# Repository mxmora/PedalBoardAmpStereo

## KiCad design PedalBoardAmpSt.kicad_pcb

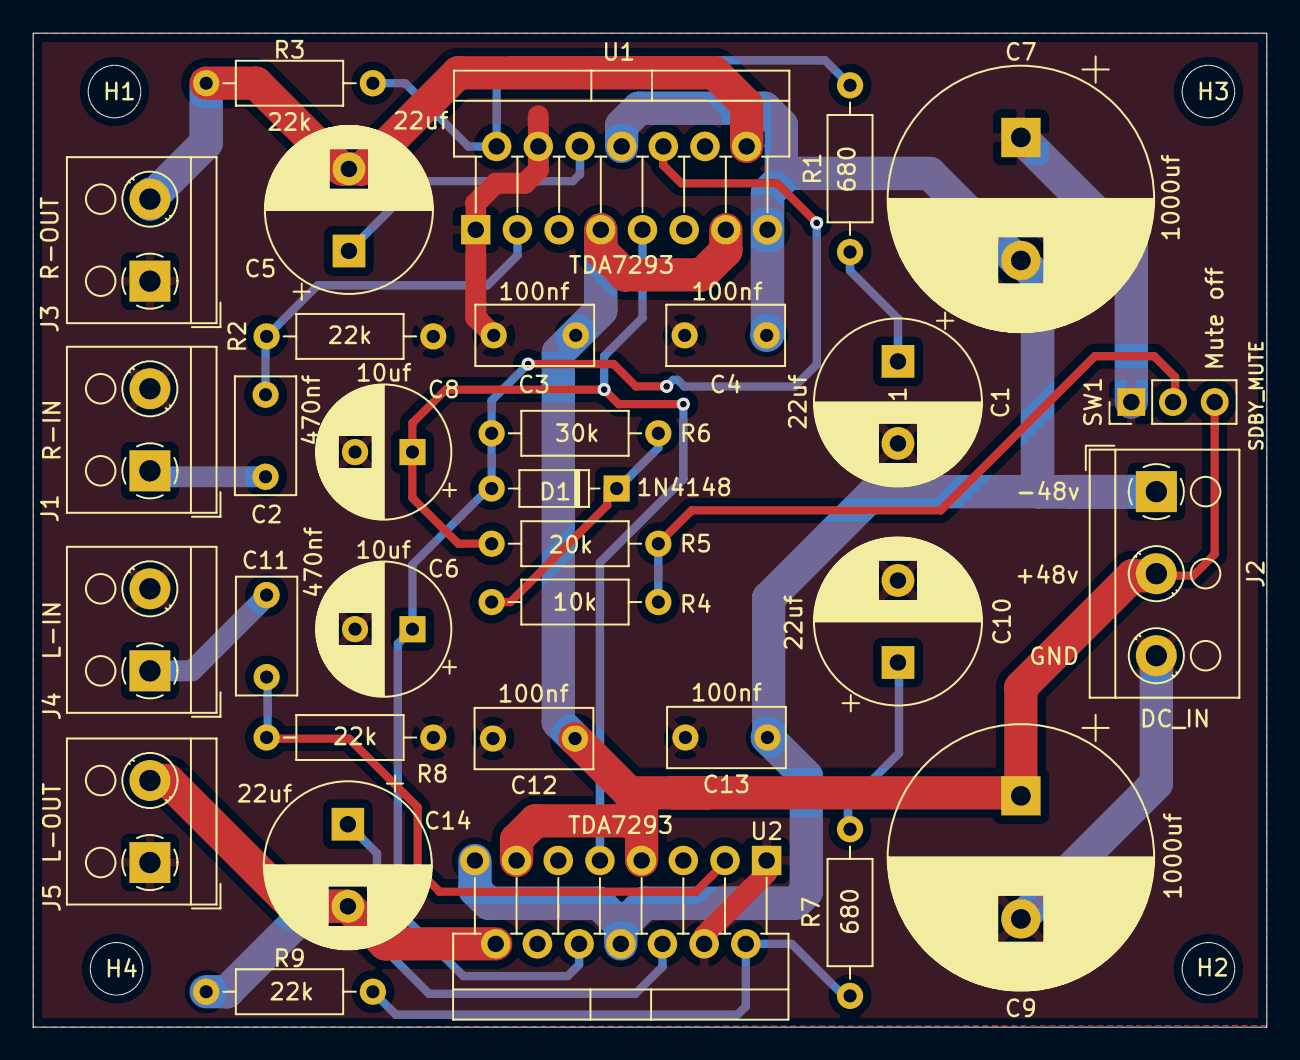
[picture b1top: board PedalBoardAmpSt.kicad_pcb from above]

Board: 2 copper layers, 75.2 x 60.6 mm, 36 parts (0 on the bottom side), 19 nets.

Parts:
C1, C5, C10, C14: 22uf; CP_Radial_D10.0mm_P5.00mm
C2, C11: 470nf; C_Rect_L7.0mm_W3.5mm_P5.00mm
C3, C4, C12, C13: 100nf; C_Rect_L7.0mm_W3.5mm_P5.00mm
C6, C8: 10uf; CP_Radial_D8.0mm_P3.50mm
C7, C9: 1000uf; CP_Radial_D16.0mm_P7.50mm
D1: 1N4148; D_DO-35_SOD27_P7.62mm_Horizontal
H1, H2, H3, H4: MountingHole; MountingHole_3.2mm_M3
J1: R-IN; TerminalBlock_RND_205-00001_1x02_P5.00mm_Horizontal
J2: DC_IN; TerminalBlock_RND_205-00002_1x03_P5.00mm_Horizontal
J3: R-OUT; TerminalBlock_RND_205-00001_1x02_P5.00mm_Horizontal
J4: L-IN; TerminalBlock_RND_205-00001_1x02_P5.00mm_Horizontal
J5: L-OUT; TerminalBlock_RND_205-00001_1x02_P5.00mm_Horizontal
R1, R7: 680; R_Axial_DIN0207_L6.3mm_D2.5mm_P10.16mm_Horizontal
R2, R3, R8, R9: 22k; R_Axial_DIN0207_L6.3mm_D2.5mm_P10.16mm_Horizontal
R4: 10k; R_Axial_DIN0207_L6.3mm_D2.5mm_P10.16mm_Horizontal
R5: 20k; R_Axial_DIN0207_L6.3mm_D2.5mm_P10.16mm_Horizontal
R6: 30k; R_Axial_DIN0207_L6.3mm_D2.5mm_P10.16mm_Horizontal
SW1: SDBY_MUTE; PinHeader_1x03_P2.54mm_Vertical
U1, U2: TDA7293; TO-220-15_P2.54x2.54mm_StaggerOdd_Lead4.58mm_Vertical

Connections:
+48vFilter: C3.1, C9.1, C12.1, J2.2, SW1.3, U1.7, U1.13, U2.7, U2.13
-48vFilter: C4.1, C7.2, C13.1, J2.1, U1.8, U1.15, U2.8, U2.15
GND: C1.2, C3.2, C4.2, C6.2, C7.1, C8.2, C9.2, C10.2, C12.2, C13.2, J1.2, J2.3, J3.1, J4.2, J5.1, R2.1, R8.1, SW1.1, U1.1, U1.4, U2.1, U2.4
MUTE: C6.1, D1.2, R6.1, U1.10, U2.10
unnamed: C1.1, R1.2
unnamed: C2.1, R2.2, U1.3
unnamed: C2.2, J1.1
unnamed: C5.1, U1.6
unnamed: C5.2, J3.2, R3.1, U1.14
unnamed: C10.1, R7.2
unnamed: C11.1, R8.2, U2.3
unnamed: C11.2, J4.1
unnamed: C14.1, U2.6
unnamed: C14.2, J5.2, R9.1, U2.14
unnamed: D1.1, R4.1, R6.2
unnamed: R1.1, R3.2, U1.2
unnamed: R4.2, R5.2, SW1.2
unnamed: R7.1, R9.2, U2.2
STBY: C8.1, R5.1, U1.9, U2.9

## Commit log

2019-11-20 first check in
2020-01-28 re-layout
2020-12-20 larger traces
2021-01-05 update design
